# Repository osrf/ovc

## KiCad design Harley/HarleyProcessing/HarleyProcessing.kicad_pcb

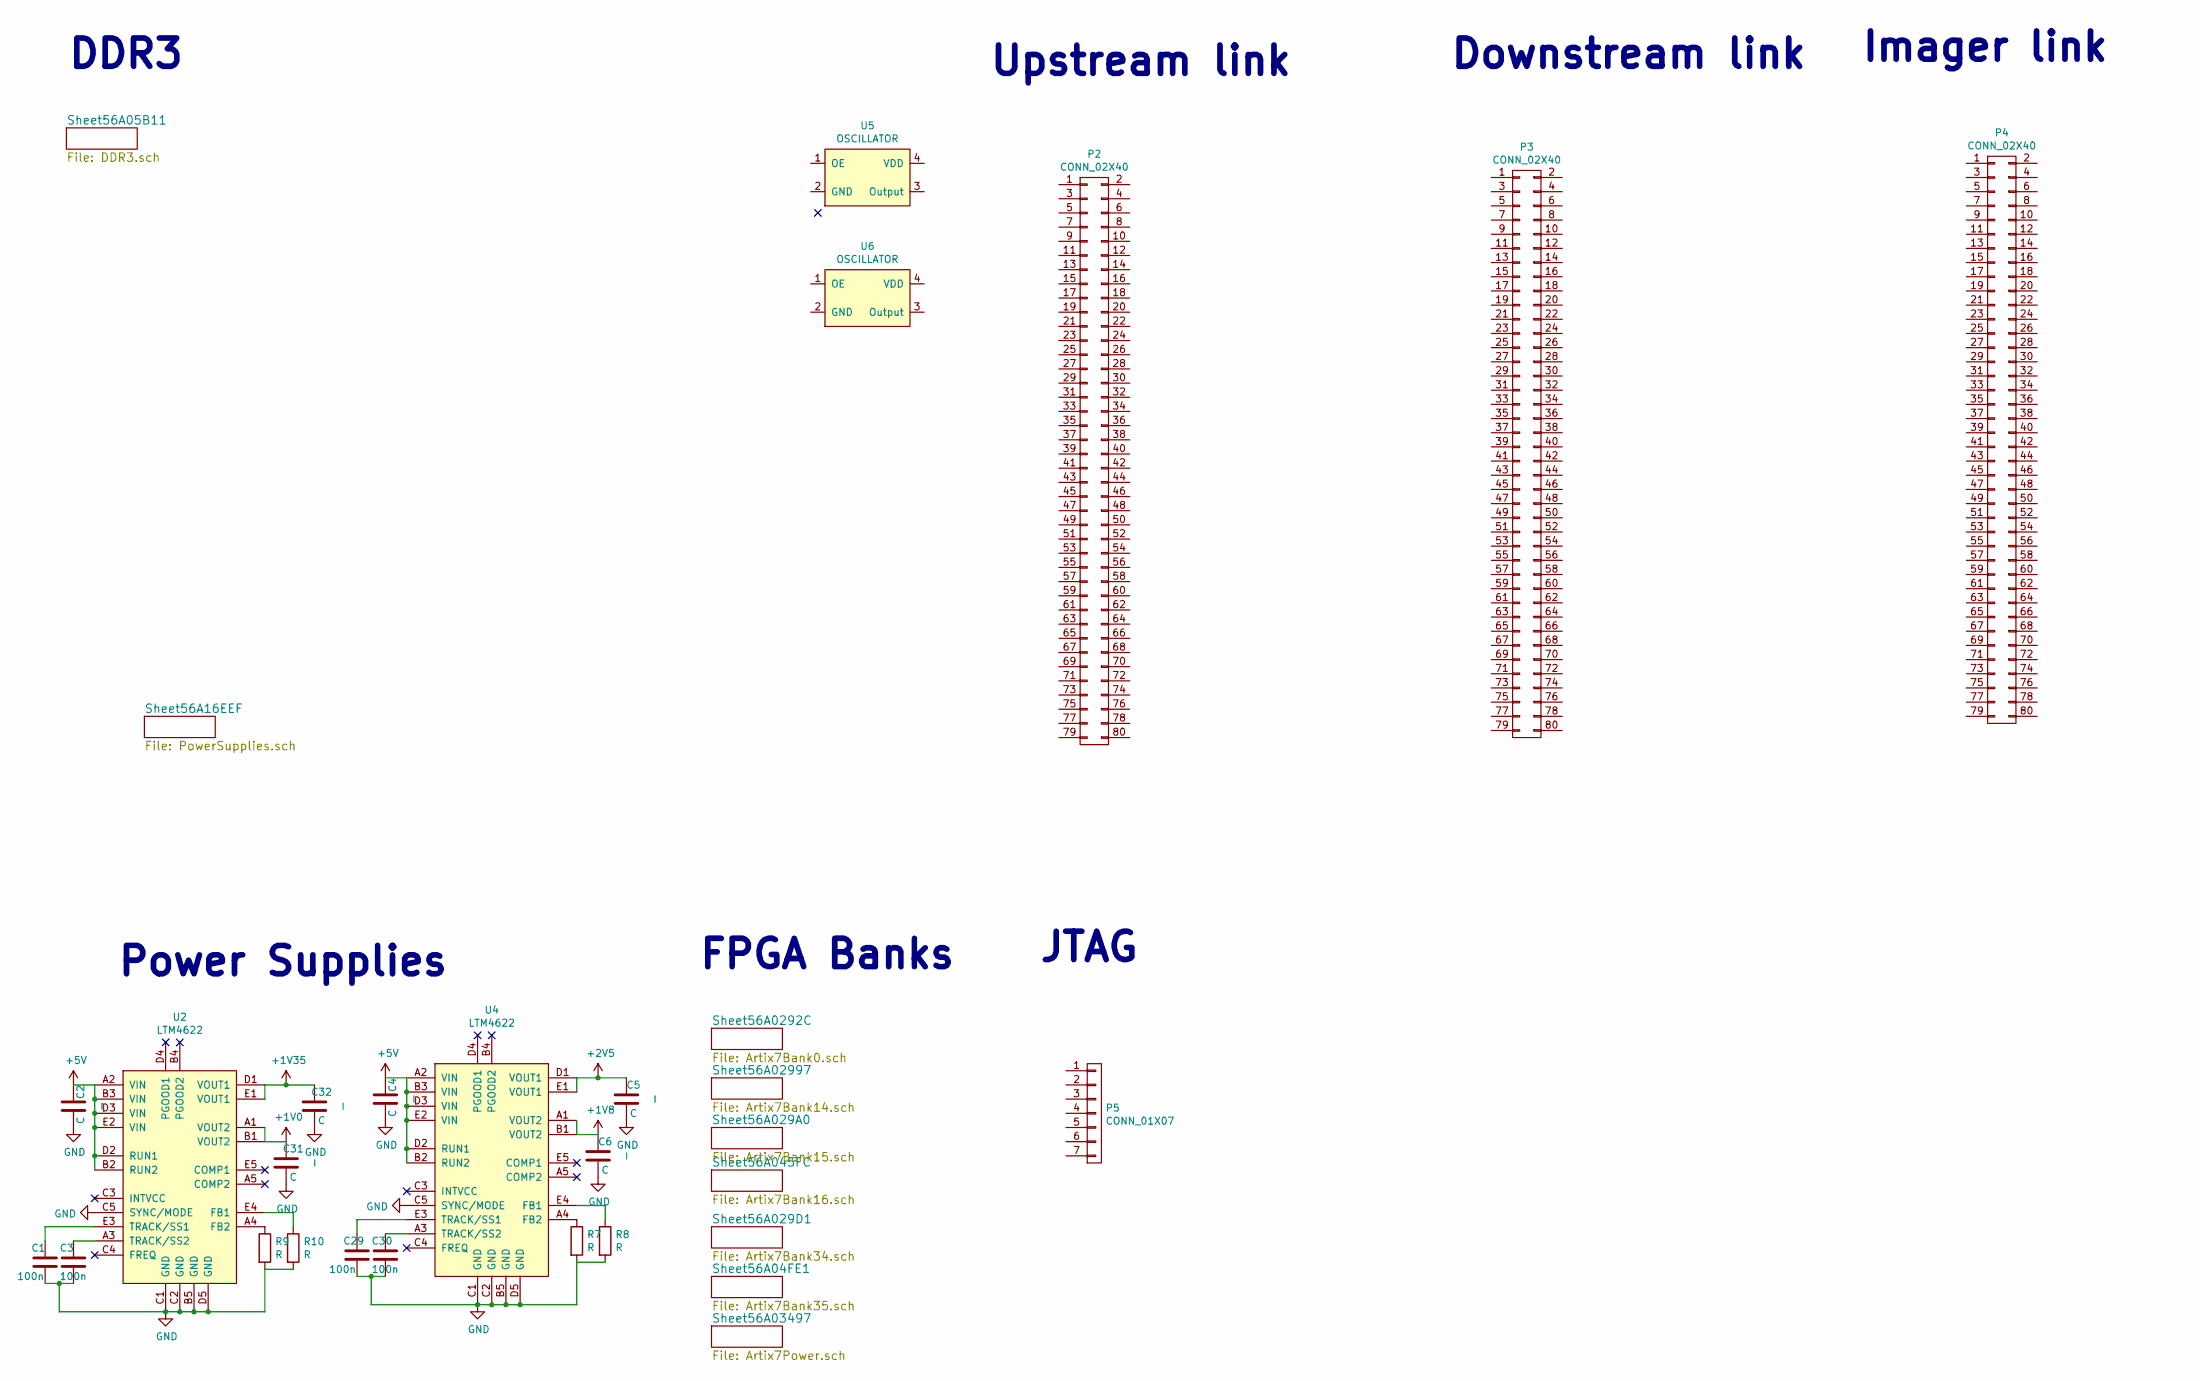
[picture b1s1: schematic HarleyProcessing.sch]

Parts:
C1, C3, C29, C30: 100n; C_0402
C2, C4: C; C_0603; Voltage _; Tolerance _
C5, C6, C31, C32: C; C_0805; Voltage _; Tolerance _
P2, P3, P4: CONN_02X40; DF40C_80DS_0-4V
P5: CONN_01X07; Pin_Header_Straight_1x07
R7, R8, R9, R10: R; R_0402
U2, U4: LTM4622; LGA25_6.25X6.25X1.82; Voltage _; Tolerance _
U5, U6: OSCILLATOR; 8y; Voltage _; Tolerance _

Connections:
+1V0: C31.2, U2.A1 (VOUT2), U2.B1 (VOUT2)
+1V8: C6.2, U4.A1 (VOUT2), U4.B1 (VOUT2)
+1V35: C32.2, U2.D1 (VOUT1), U2.E1 (VOUT1)
+2V5: C5.2, U4.D1 (VOUT1), U4.E1 (VOUT1)
+5V: C2.2, C4.2, U2.A2 (VIN), U2.B2 (RUN2), U2.B3 (VIN), U2.D2 (RUN1), U2.D3 (VIN), U2.E2 (VIN), U4.A2 (VIN), U4.B2 (RUN2), U4.B3 (VIN), U4.D2 (RUN1), U4.D3 (VIN), U4.E2 (VIN)
GND: C1.2, C2.1, C3.2, C4.1, C5.1, C6.1, C29.2, C30.2, C31.1, C32.1, R7.2, R8.2, R9.2, R10.2, U2.B5 (GND), U2.C1 (GND), U2.C2 (GND), U2.C5 (SYNC/MODE), U2.D5 (GND), U4.B5 (GND), U4.C1 (GND), U4.C2 (GND), U4.C5 (SYNC/MODE), U4.D5 (GND); also elsewhere on the board
unnamed: C1.1, U2.E3 (TRACK/SS1)
unnamed: C3.1, U2.A3 (TRACK/SS2)
unnamed: C29.1, U4.E3 (TRACK/SS1)
unnamed: C30.1, U4.A3 (TRACK/SS2)
unnamed: R7.1, U4.A4 (FB2)
unnamed: R8.1, U4.E4 (FB1)
unnamed: R9.1, U2.A4 (FB2)
unnamed: R10.1, U2.E4 (FB1)

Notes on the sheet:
Power Supplies
FPGA Banks
Upstream link
Downstream link
JTAG
Imager link
DDR3

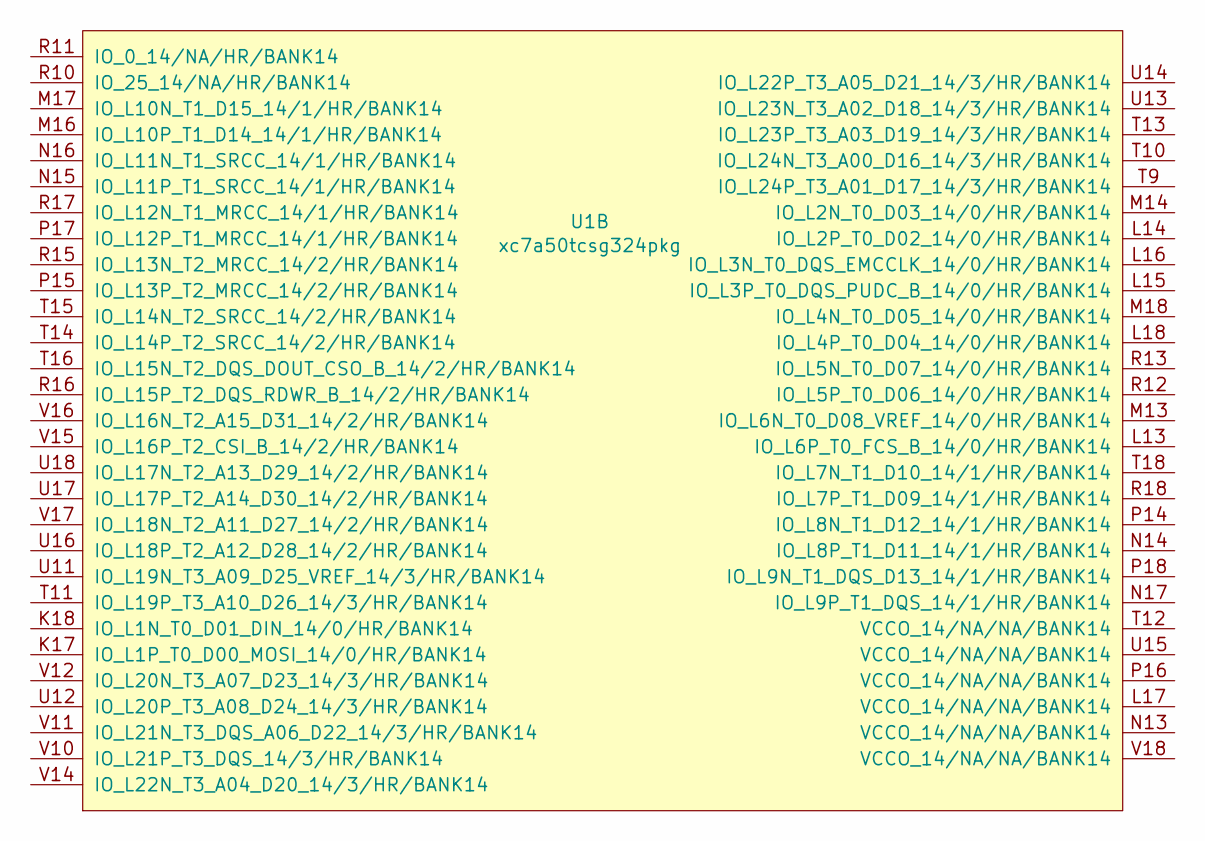
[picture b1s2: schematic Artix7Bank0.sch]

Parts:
U1: xc7a50tcsg324pkg; BGA324C80P18X18_1500X1500X150; Voltage _; Tolerance _

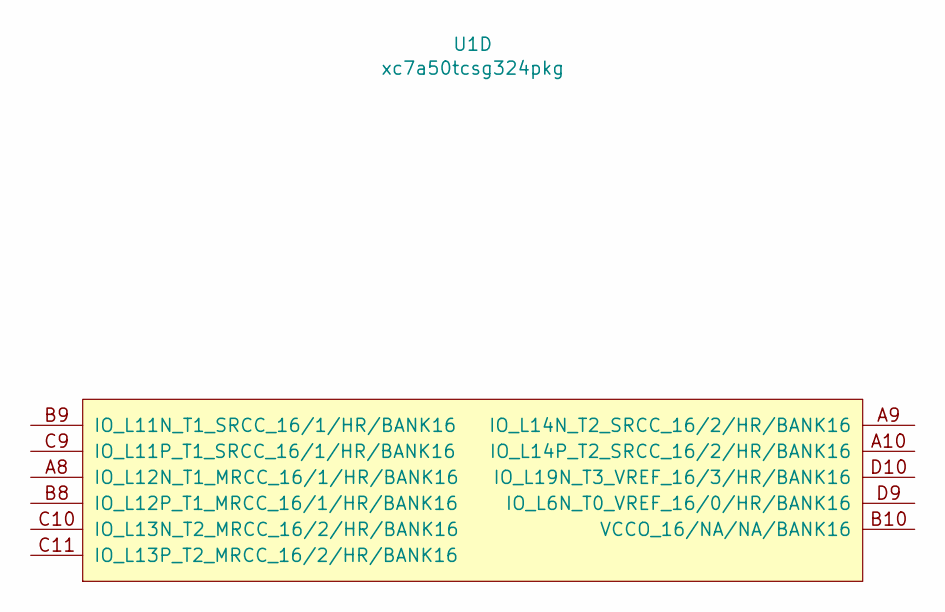
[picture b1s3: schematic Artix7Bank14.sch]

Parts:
U1: xc7a50tcsg324pkg; BGA324C80P18X18_1500X1500X150; Voltage _; Tolerance _

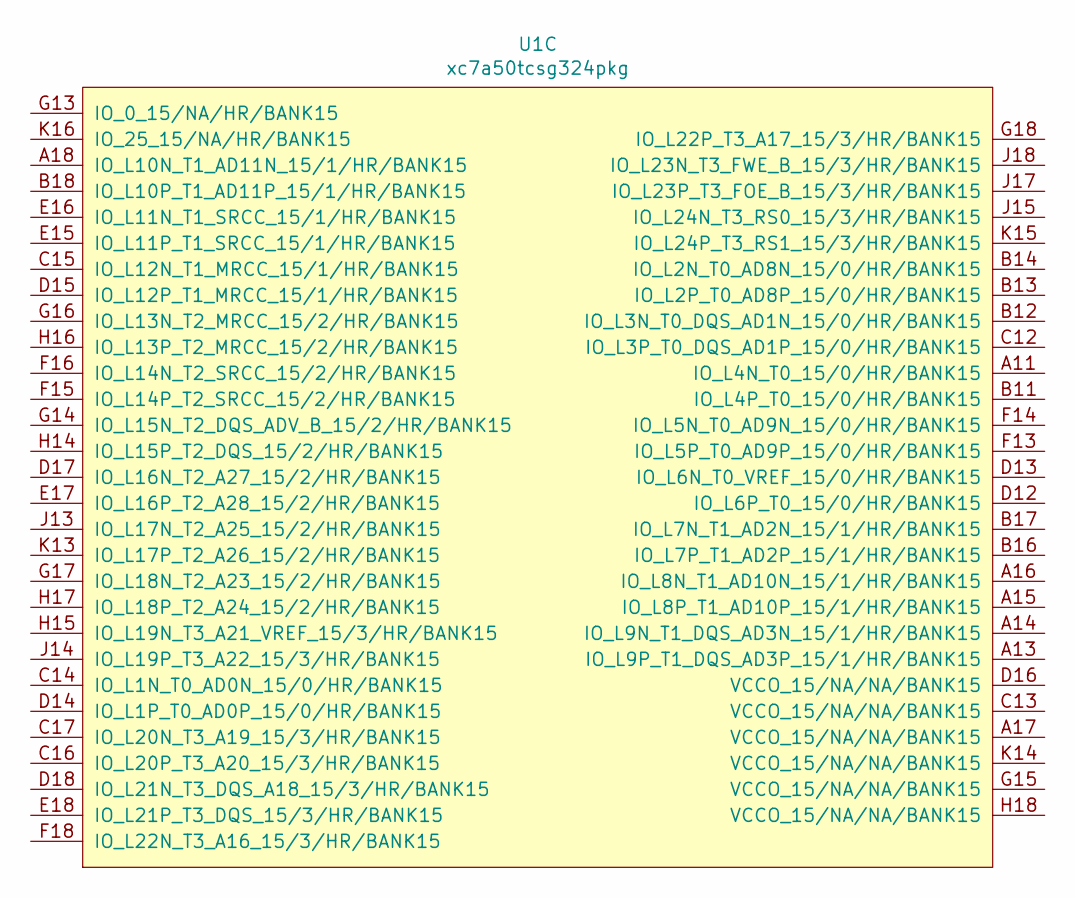
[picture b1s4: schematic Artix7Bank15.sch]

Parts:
U1: xc7a50tcsg324pkg; BGA324C80P18X18_1500X1500X150; Voltage _; Tolerance _

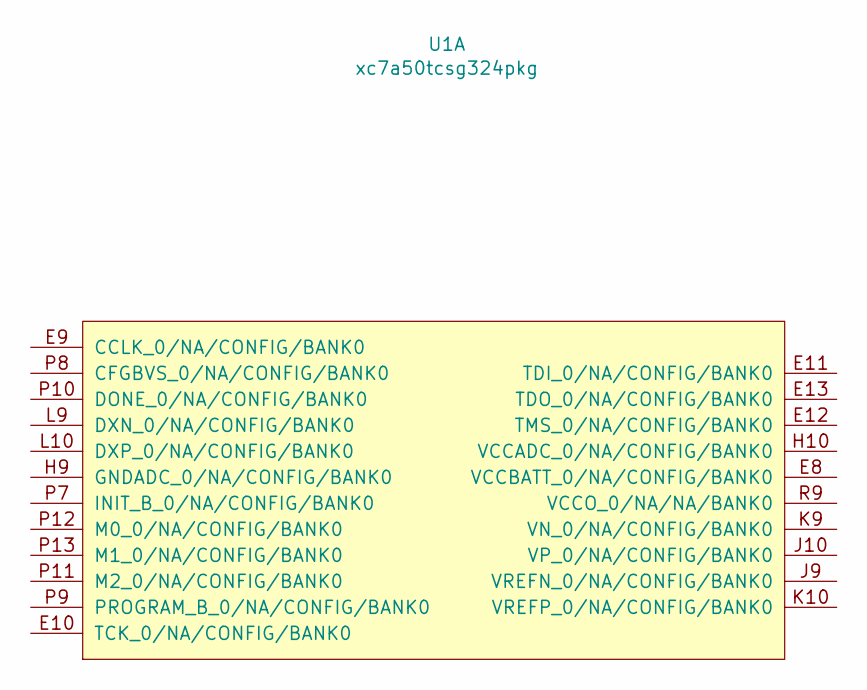
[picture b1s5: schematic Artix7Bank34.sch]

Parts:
U1: xc7a50tcsg324pkg; BGA324C80P18X18_1500X1500X150; Voltage _; Tolerance _

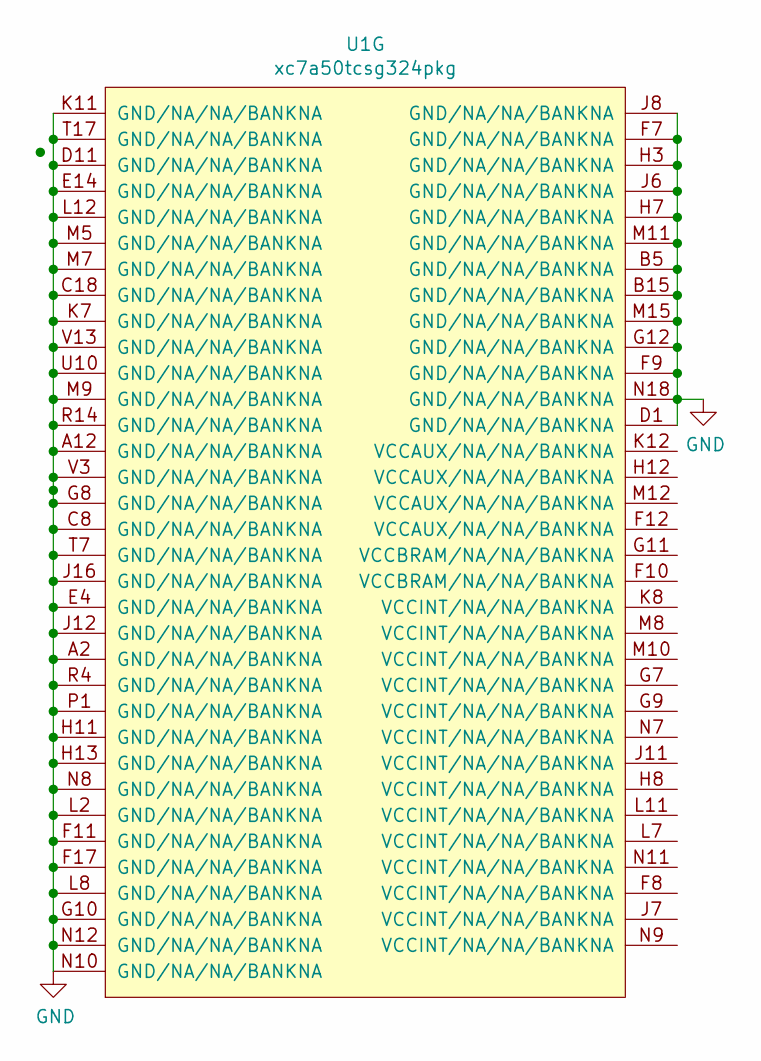
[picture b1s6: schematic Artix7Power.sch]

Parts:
U1: xc7a50tcsg324pkg; BGA324C80P18X18_1500X1500X150; Voltage _; Tolerance _

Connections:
GND: U1.A2 (GND/NA/NA/BANKNA), U1.A12 (GND/NA/NA/BANKNA), U1.B5 (GND/NA/NA/BANKNA), U1.B15 (GND/NA/NA/BANKNA), U1.C8 (GND/NA/NA/BANKNA), U1.C18 (GND/NA/NA/BANKNA), U1.D1 (GND/NA/NA/BANKNA), U1.D11 (GND/NA/NA/BANKNA), U1.E4 (GND/NA/NA/BANKNA), U1.E14 (GND/NA/NA/BANKNA), U1.F7 (GND/NA/NA/BANKNA), U1.F9 (GND/NA/NA/BANKNA), U1.F11 (GND/NA/NA/BANKNA), U1.F17 (GND/NA/NA/BANKNA), U1.G8 (GND/NA/NA/BANKNA), U1.G10 (GND/NA/NA/BANKNA), U1.G12 (GND/NA/NA/BANKNA), U1.H3 (GND/NA/NA/BANKNA), U1.H7 (GND/NA/NA/BANKNA), U1.H11 (GND/NA/NA/BANKNA), U1.H13 (GND/NA/NA/BANKNA), U1.J6 (GND/NA/NA/BANKNA), U1.J8 (GND/NA/NA/BANKNA), U1.J12 (GND/NA/NA/BANKNA), U1.J16 (GND/NA/NA/BANKNA), U1.K7 (GND/NA/NA/BANKNA), U1.K11 (GND/NA/NA/BANKNA), U1.L2 (GND/NA/NA/BANKNA), U1.L8 (GND/NA/NA/BANKNA), U1.L12 (GND/NA/NA/BANKNA), U1.M5 (GND/NA/NA/BANKNA), U1.M7 (GND/NA/NA/BANKNA), U1.M9 (GND/NA/NA/BANKNA), U1.M11 (GND/NA/NA/BANKNA), U1.M15 (GND/NA/NA/BANKNA), U1.N8 (GND/NA/NA/BANKNA), U1.N10 (GND/NA/NA/BANKNA), U1.N12 (GND/NA/NA/BANKNA), U1.N18 (GND/NA/NA/BANKNA), U1.P1 (GND/NA/NA/BANKNA), U1.R4 (GND/NA/NA/BANKNA), U1.R14 (GND/NA/NA/BANKNA), U1.T7 (GND/NA/NA/BANKNA), U1.T17 (GND/NA/NA/BANKNA), U1.U10 (GND/NA/NA/BANKNA), U1.V3 (GND/NA/NA/BANKNA), U1.V13 (GND/NA/NA/BANKNA); also elsewhere on the board

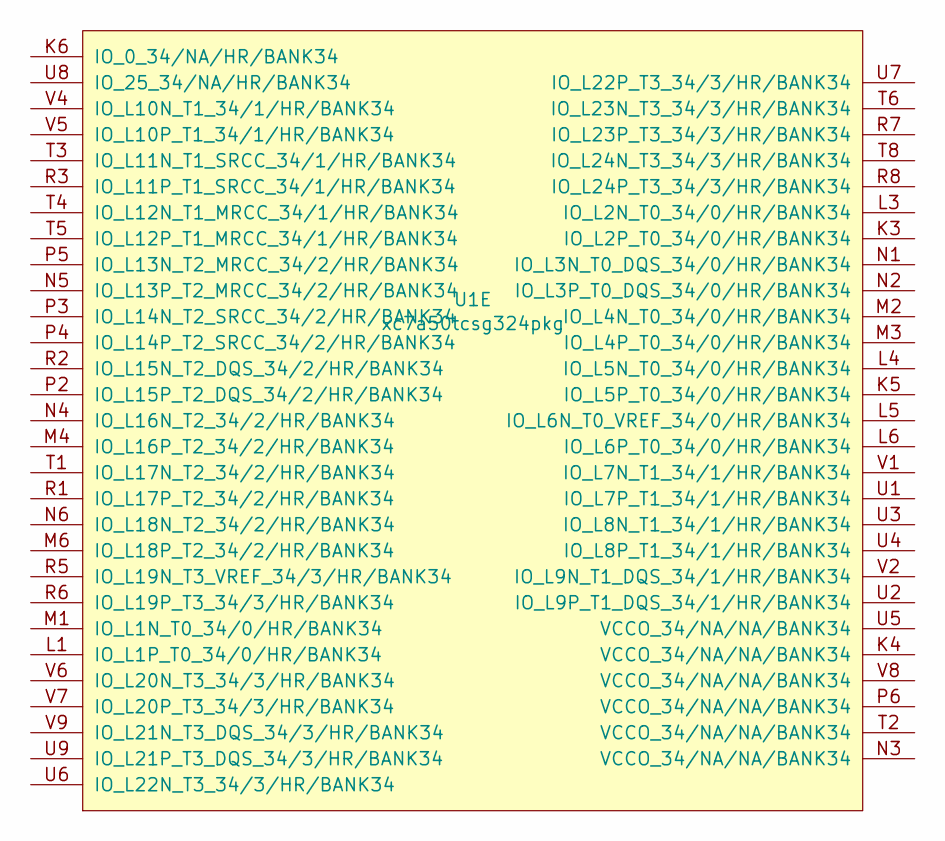
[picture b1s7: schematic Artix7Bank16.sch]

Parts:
U1: xc7a50tcsg324pkg; BGA324C80P18X18_1500X1500X150; Voltage _; Tolerance _

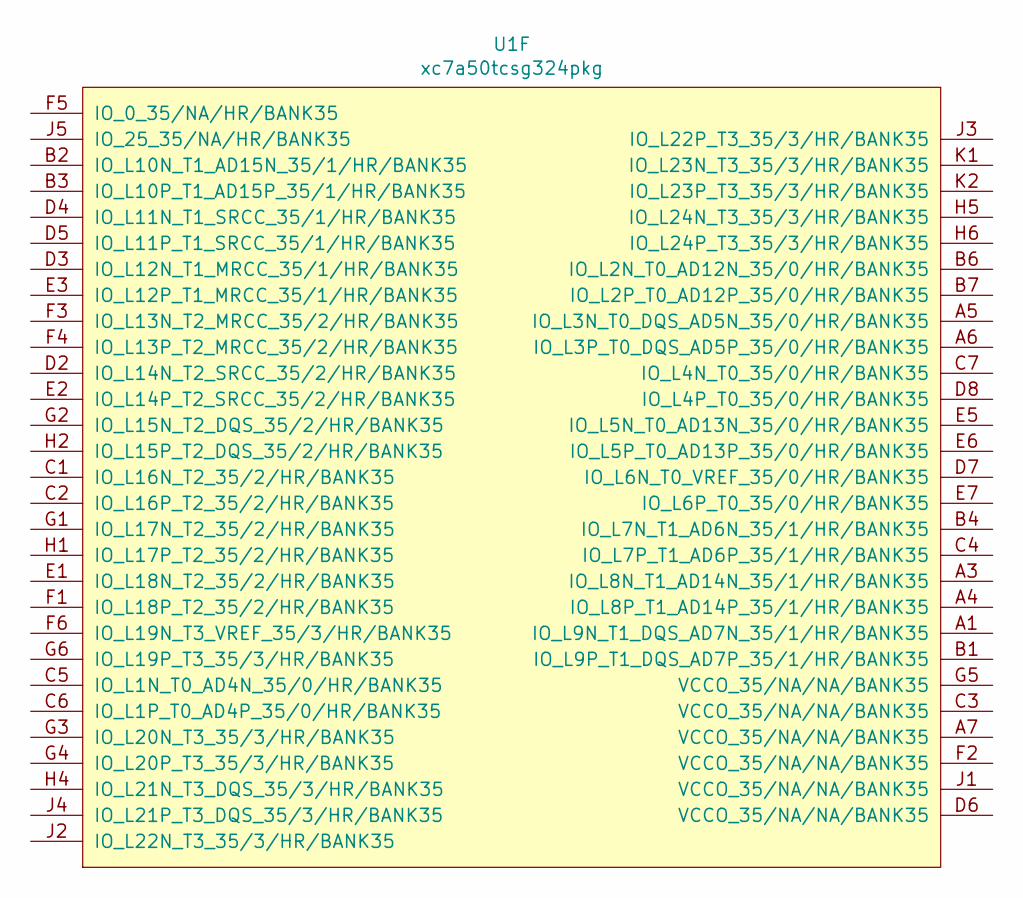
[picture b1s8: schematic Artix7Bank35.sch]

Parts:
U1: xc7a50tcsg324pkg; BGA324C80P18X18_1500X1500X150; Voltage _; Tolerance _

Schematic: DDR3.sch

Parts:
C7, C23: 1u; C_0201; Voltage 6.3; Tolerance 20%
C8, C10, C12, C27, C28: 10n; C_0201; Voltage 10; Tolerance 10%
C9, C11, C13, C15, C17, C19: 2.2n; C_0201; Voltage 25; Tolerance 10%
C14, C16, C18: 100n; C_0201; Voltage 6.3; Tolerance 10%
C20, C22, C25: 470n; C_0201; Voltage 6.3; Tolerance 10%
C21: 3.3n; C_0201; Voltage 25; Tolerance 10%
C24: 4.7n; C_0201; Voltage 16; Tolerance 10%
C26: 22u; C_0805; Voltage 6.3; Tolerance 10%
R1: 4.7k; C_0201; Voltage _; Tolerance 1%
R2: 80.6; R_0402; Voltage _; Tolerance 1%
R3, R4: 1k; C_0201; Voltage _; Tolerance 1%
R5: 240; C_0201; Voltage _; Tolerance 1%
R6: 2k; C_0201; Voltage _; Tolerance 1%
U3: MT41K128M16; WBGA96C80P6X16_90X1300X120; Voltage _; Tolerance _

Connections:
DDR_A0: U3.N3 (A0)
DDR_A1: U3.P7 (A1)
DDR_A2: U3.P3 (A2)
DDR_A3: U3.N2 (A3)
DDR_A4: U3.P8 (A4)
DDR_A5: U3.P2 (A5)
DDR_A6: U3.R8 (A6)
DDR_A7: U3.R2 (A7)
DDR_A8: U3.T8 (A8)
DDR_A9: U3.R3 (A9)
DDR_A10: U3.L7 (A10/AP)
DDR_A11: U3.R7 (A11)
DDR_A12: U3.N7 (A12/BC#)
DDR_A13: U3.T3 (A13)
DDR_BA0: U3.M2 (BA0)
DDR_BA1: U3.N8 (BA1)
DDR_BA2: U3.M3 (BA2)
DDR_CAS#: U3.K3 (CAS#)
DDR_CKE: R1.1, U3.K9 (CKE)
DDR_CLK+: R2.1, U3.J7 (CK+)
DDR_CLK-: R2.2, U3.K7 (CK-)
DDR_DQL0: U3.E3 (DQL0)
DDR_DQL1: U3.F7 (DQL1)
DDR_DQL2: U3.F2 (DQL2)
DDR_DQL3: U3.F8 (DQL3)
DDR_DQL4: U3.H3 (DQL4)
DDR_DQL5: U3.H8 (DQL5)
DDR_DQL6: U3.G2 (DQL6)
DDR_DQL7: U3.H7 (DQL7)
DDR_DQSL+: U3.F3 (DQSL+)
DDR_DQSL-: U3.G3 (DQSL-)
DDR_DQSU+: U3.C7 (DQSU+)
DDR_DQSU-: U3.B7 (DQSU-)
DDR_DQU0: U3.D7 (DQU0)
DDR_DQU1: U3.C3 (DQU1)
DDR_DQU2: U3.C8 (DQU2)
DDR_DQU3: U3.C2 (DQU3)
DDR_DQU4: U3.A7 (DQU4)
DDR_DQU5: U3.A2 (DQU5)
DDR_DQU6: U3.B8 (DQU6)
DDR_DQU7: U3.A3 (DQU7)
DDR_ODT: U3.K1 (ODT)
DDR_RAS#: U3.J3 (RAS#)
DDR_RST#: R6.2, U3.T2 (RST#)
DDR_VDD: C9.1, C10.1, C11.1, C12.1, C13.1, C14.1, C15.1, C16.1, C17.1, C18.1, C19.1, C20.1, C21.1, C22.1, C23.1, C24.1, C25.1, C26.1, C27.1, C28.1, R3.1, R6.1, U3.A1 (VDDQ), U3.A8 (VDDQ), U3.B2 (VDD), U3.C1 (VDDQ), U3.C9 (VDDQ), U3.D2 (VDDQ), U3.D9 (VDD), U3.E9 (VDDQ), U3.F1 (VDDQ), U3.G7 (VDD), U3.H2 (VDDQ), U3.H9 (VDDQ), U3.K2 (VDD), U3.K8 (VDD), U3.N1 (VDD), U3.N9 (VDD), U3.R1 (VDD), U3.R9 (VDD)
DDR_VREF: C7.1, C8.1, R3.2, R4.1, U3.H1 (VREFDQ), U3.M8 (VREFCA)
DDR_WE#: U3.L3 (WE#)
GND: C7.2, C8.2, C9.2, C10.2, C11.2, C12.2, C13.2, C14.2, C15.2, C16.2, C17.2, C18.2, C19.2, C20.2, C21.2, C22.2, C23.2, C24.2, C25.2, C26.2, C27.2, C28.2, R1.2, R4.2, R5.2, U3.A9 (VSS), U3.B1 (VSSQ), U3.B3 (VSS), U3.B9 (VSSQ), U3.D1 (VSSQ), U3.D3 (DMU), U3.D8 (VSSQ), U3.E1 (VSS), U3.E2 (VSSQ), U3.E7 (DML), U3.E8 (VSSQ), U3.F9 (VSSQ), U3.G1 (VSSQ), U3.G8 (VSS), U3.G9 (VSSQ), U3.J2 (VSS), U3.J8 (VSS), U3.L2 (CS#), U3.M1 (VSS), U3.M9 (VSS), U3.P1 (VSS), U3.P9 (VSS), U3.T1 (VSS), U3.T9 (VSS); also elsewhere on the board
unnamed: R5.1, U3.L8 (ZQ)

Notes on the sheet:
SDRAM DDR3L

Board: 2 copper layers, 51 parts (1 on the bottom side), 21 nets, no tracks yet.

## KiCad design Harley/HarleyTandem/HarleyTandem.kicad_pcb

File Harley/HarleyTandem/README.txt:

Project: harley_tandem, rev. B
(This is a trinocular camera sensor board.)

=============================
PCB Fabrication notes:
=============================
* Lead time: 4 days
* Board outline is a rectangle with a rectangular protrusion on the north side.
* Bounding box is 9.40" x 1.54"
* 6 layers:
  * layer 1 = signal with 7-mil 50-ohm traces relative to layer 2
  * layer 2 = full plane
  * layer 3 = mixed (signal and partial planes)
  * layer 4 = mixed (signal and partial planes)
  * layer 5 = full plane
  * layer 6 = signal with 7-mil 50-ohm traces relative to layer 5
* Controlled stackup, using the included "harley_tandem_stackup_rev_b.pdf" report
  generated by Sierra's "HDI Stackup Planner" website. PLEASE NOTE however that
  I was unable to generate the report I wanted from the website; we want 7-mil
  traces on the outer layers (1 & 6) to be 50 ohm +/- 10% with respect to the
  planes on layers 2 & 5. This will likely need a slightly different stackup
  than that shown on the report.
  * 61mil PCB thickness.
  * 7mil traces on outer layer (1 & 6) need to be 50 ohm +/- 10% with respect to
    the planes on layers 2 & 5. The dielectric thickness between
    layers 1&2 and 5&6 will likely need to be slightly thicker than shown on
    the report to get within 10% (or better) of 50mil impedance.
* Layer thicknesses as specified in the stackup report: { 1, 1, 0.5, 0.5, 1, 1 }
* Minimum trace/space is 5mil.
* All holes plated
* Minimum via-drill 8 mil, minimum via-pad 16 mil. Most vias are >= 24mil
* FR4 material
* HASL finish
* Green soldermask both sides
* White silkscreen both sides
* RoHS processing is fine but not necessary; these are laboratory prototypes.

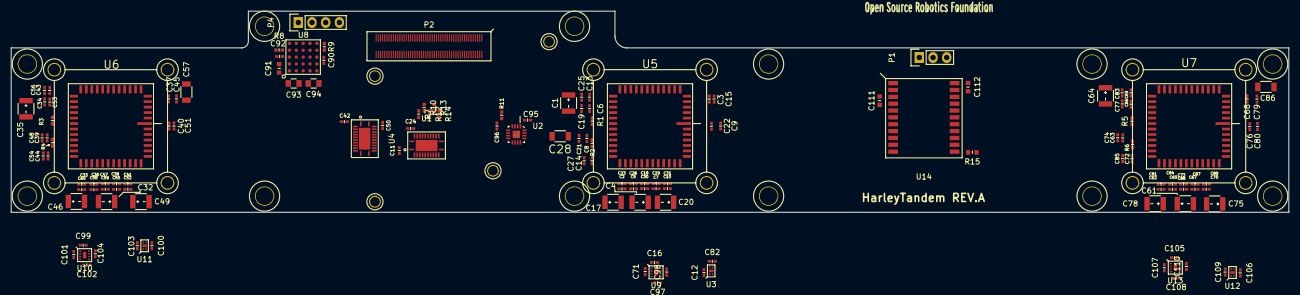
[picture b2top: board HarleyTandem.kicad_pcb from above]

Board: 6 copper layers, 237.0 x 37.3 mm, 144 parts (0 on the bottom side), 100 nets, no tracks yet.

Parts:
C1, C4, C17, C20, C32, C35, C46, C49, C61, C64, C75, C78: 100u; C_1210Polarized
C2, C5, C7, C10, C15, C19, C21, C22, C25, C27, C30, C33, C36, C38, C41, C45, C48, C51, C53, C54, C56, C59, C62, C65, C67, C70, C74, C77, C79, C80, C83, C85, C88: 4.7u; C_0402
C3, C6, C8, C11, C24, C34, C37, C39, C42, C50, C63, C66, C68, C71, C101, C107: 100n; C_0402
C9, C12, C13, C14, C16, C18, C23, C26, C29, C31, C40, C43, C44, C47, C52, C55, C58, C60, C69, C72, C73, C76, C81, C82, C84, C87, C89, C95, C96, C97, C98, C99, C100, C102, C103, C104, C105, C106, C108, C109, C110: 1u; C_0402
C28, C57, C86: 10u; C_1206
C90, C92: 10n; C_0402
C91: 10u; C_0603
C93, C94: 47u; C_0805
C111, C112: 100n; C_0603
P1: CONN_01X03; Pin_Header_Straight_1x03
P2: CONN_02X50; DF40C_100DS_0-4V
P4: CONN_01X04; Pin_Header_Straight_1x04
R1, R3, R5, R11: 100; R_0402
R2, R4, R6: 47k; R_0402
R7, R10, R12, R13, R14: 50; R_0402
R8: 12.4k; R_0402
R9: 25.5k; R_0402
R15: 10k; R_0603
U1, U4: 74AVCH8T245-1EP; QFN-24-1EP-Pitch0.5-nonSquare
U2: SI53306; QFN-16-1EP_3x3mm_Pitch0.5mm
U3, U11, U12: mic5302; MLF4
U5, U6, U7: NOIP1SN1300A-QDI; LCC101.6P1422X1422X165-48
U8: LTM4622; LGA25_6.25X6.25X1.82
U9, U10, U13: mic5330; MLF8
U14: uIMU-2; DFP-22_0.5mmPitch_125x155mm

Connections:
2V0: C12.1, C94.2, C100.1, C106.1, P4.3, U3.1, U3.3, U8.D1, U8.E1, U11.1, U11.3, U12.1, U12.3
3V5: C11.1, C16.1, C42.1, C93.2, C99.1, C105.1, C111.1, C112.1, P4.2, R15.1, U1.1, U4.1, U4.2, U8.A1, U8.B1, U9.1, U9.4, U9.5, U10.1, U10.4, U10.5, U13.1, U13.4, U13.5, U14.3, U14.22
+2V5: C24.1, C50.1, C95.2, C96.1, P2.81, P2.83, P2.85, U1.23, U1.24, U2.1, U2.5, U2.16, U4.23, U4.24
+5V: C91.2, P2.87, P2.89, P2.91, P2.93, P2.95, P2.97, P2.99, P4.1, U8.A2, U8.B2, U8.B3, U8.D2, U8.D3, U8.E2
GND: C1.2, C2.2, C3.2, C4.2, C5.2, C6.2, C7.2, C8.2, C9.2, C10.2, C11.2, C12.2, C13.2, C14.2, C15.2, C16.2, C17.2, C18.2, C19.2, C20.2, C21.2, C22.2, C23.2, C24.2, C25.2, C26.2, C27.2, C28.2, C29.2, C30.2, C31.2, C32.2, C33.2, C34.2, C35.2, C36.2, C37.2, C38.2, C39.2, C40.2, C41.2, C42.2, C43.2, C44.2, C45.2, C46.2, C47.2, C48.2, C49.2, C50.2, C51.2, C52.2, C53.2, C54.2, C55.2, C56.2, C57.2, C58.2, C59.2, C60.2, C61.2, C62.2, C63.2, C64.2, C65.2, C66.2, C67.2, C68.2, C69.2, C70.2, C71.2, C72.2, C73.2, C74.2, C75.2, C76.2, C77.2, C78.2, C79.2, C80.2, C81.2, C82.2, C83.2, C84.2, C85.2, C86.2, C87.2, C88.2, C89.2, C90.2, C91.1, C92.2, C93.1, C94.1, C95.1, C96.2, C97.2, C98.2, C99.2, C100.2, C101.2, C102.2, C103.2, C104.2, C105.2, C106.2, C107.2, C108.2, C109.2, C110.2, C111.2, C112.2, P1.3, P2.1, P2.3, P2.5, P2.6, P2.7, P2.12, P2.13, P2.18, P2.19, P2.24, P2.25, P2.30, P2.31, P2.36, P2.37, P2.42, P2.43, P2.48, P2.49, P2.54, P2.60, P2.66, P2.72, P2.79, P2.86, P2.90, P4.4, R2.2, R4.2, R6.2, R8.2, R9.2, U1.2, U1.11, U1.12, U1.13, U1.22, U1.25, U2.4, U2.8, U2.13, U2.17, U3.2, U3.EPAD, U4.11, U4.12, U4.13, U4.14, U4.15, U4.21, U4.22, U4.25, U5.5, U5.20, U5.21, U5.25, U5.27, U5.30, U5.32, U5.34, U5.35, U5.37, U5.39, U5.42, U5.43, U5.48, U6.5, U6.20, U6.21, U6.25, U6.27, U6.30, U6.32, U6.34, U6.35, U6.37, U6.39, U6.42, U6.43, U6.48, U7.5, U7.20, U7.21, U7.25, U7.27, U7.30, U7.32, U7.34, U7.35, U7.37, U7.39, U7.42, U7.43, U7.48, U8.B5, U8.C1, U8.C2, U8.D5, U9.2, U9.EPAD, U10.2, U10.EPAD, U11.2, U11.EPAD, U12.2, U12.EPAD, U13.2, U13.EPAD, U14.11, U14.21
IMU_RX0: P1.2, U14.18
IMU_RX1: U1.10, U14.6
IMU_TX0: P1.1, U14.19
IMU_TX1: U4.8, U14.7
unnamed: C71.1, U9.3
unnamed: C90.1, U8.E3
unnamed: C92.1, U8.A3
unnamed: C101.1, U10.3
unnamed: C107.1, U13.3
unnamed: R2.1, U5.28
unnamed: R4.1, U6.28
unnamed: R6.1, U7.28
unnamed: R7.2, U1.21
unnamed: R8.1, U8.A4
unnamed: R9.1, U8.E4
unnamed: R10.2, U1.20
unnamed: R12.2, U1.19
unnamed: R13.2, U1.18
unnamed: R14.2, U1.17
unnamed: R15.2, U14.12
Python1_1V8: C3.1, C6.1, C8.1, C15.1, C19.1, C21.1, C28.1, C82.1, U3.4, U5.6, U5.22, U5.26
Python1_CS#: P2.82, R13.1
Python1_CS#_3V3: U1.6, U5.47
Python1_DOUT0+: P2.44, U5.9
Python1_DOUT0-: P2.46, U5.10
Python1_DOUT1+: P2.50, U5.11
Python1_DOUT1-: P2.52, U5.12
Python1_DOUT2+: P2.56, U5.13
Python1_DOUT2-: P2.58, U5.14
Python1_DOUT3+: P2.62, U5.15
Python1_DOUT3-: P2.64, U5.16
Python1_Monitor: P2.96, U4.18
Python1_Monitor_3V3: U4.6, U5.44
Python1_SYNC+: P2.68, U5.17
Python1_SYNC-: P2.70, U5.18
Python1_VDD: C1.1, C4.1, C9.1, C13.1, C14.1, C18.1, C22.1, C25.1, C27.1, C30.1, C97.1, U5.1, U5.19, U5.29, U5.36, U9.8
Python1_VDDPIX: C2.1, C5.1, C7.1, C10.1, C17.1, C20.1, C23.1, C26.1, C29.1, C31.1, C98.1, U5.31, U5.33, U5.38, U5.40, U9.7
Python1_clk_return+: P2.38, U5.7
Python1_clk_return-: P2.40, U5.8
Python1_lvds_clk+: R1.2, U2.14, U5.24
Python1_lvds_clk-: R1.1, U2.15, U5.23
Python2_1V8: C34.1, C37.1, C39.1, C45.1, C48.1, C53.1, C57.1, C103.1, U6.6, U6.22, U6.26, U11.4
Python2_CS#: P2.84, R12.1
Python2_CS#_3V3: U1.5, U6.47
Python2_DOUT0+: P2.17, U6.9
Python2_DOUT0-: P2.15, U6.10
Python2_DOUT1+: P2.11, U6.11
Python2_DOUT1-: P2.9, U6.12
Python2_DOUT2+: P2.21, U6.13
Python2_DOUT2-: P2.23, U6.14
Python2_DOUT3+: P2.27, U6.15
Python2_DOUT3-: P2.29, U6.16
Python2_Monitor: P2.98, U4.19
Python2_Monitor_3V3: U4.5, U6.44
Python2_SYNC+: P2.35, U6.17
Python2_SYNC-: P2.33, U6.18
Python2_VDD: C32.1, C35.1, C40.1, C43.1, C44.1, C47.1, C51.1, C54.1, C56.1, C59.1, C102.1, U6.1, U6.19, U6.29, U6.36, U10.8
Python2_VDDPIX: C33.1, C36.1, C38.1, C41.1, C46.1, C49.1, C52.1, C55.1, C58.1, C60.1, C104.1, U6.31, U6.33, U6.38, U6.40, U10.7
Python2_clk_return+: P2.39, U6.7
Python2_clk_return-: P2.41, U6.8
Python2_lvds_clk+: R3.2, U2.7, U6.24
Python2_lvds_clk-: R3.1, U2.6, U6.23
Python3_1V8: C63.1, C66.1, C68.1, C74.1, C77.1, C79.1, C86.1, C109.1, U7.6, U7.22, U7.26, U12.4
Python3_CS#: P2.80, R14.1
Python3_CS#_3V3: U1.7, U7.47
Python3_DOUT0+: P2.8, U7.9
Python3_DOUT0-: P2.10, U7.10
Python3_DOUT1+: P2.14, U7.11
Python3_DOUT1-: P2.16, U7.12
Python3_DOUT2+: P2.34, U7.13
Python3_DOUT2-: P2.32, U7.14
Python3_DOUT3+: P2.28, U7.15
Python3_DOUT3-: P2.26, U7.16
Python3_Monitor: P2.100, U4.20
Python3_Monitor_3V3: U4.4, U7.44
Python3_SYNC+: P2.22, U7.17
Python3_SYNC-: P2.20, U7.18
Python3_VDD: C61.1, C64.1, C69.1, C72.1, C73.1, C76.1, C80.1, C83.1, C85.1, C88.1, C108.1, U7.1, U7.19, U7.29, U7.36, U13.8
Python3_VDDPIX: C62.1, C65.1, C67.1, C70.1, C75.1, C78.1, C81.1, C84.1, C87.1, C89.1, C110.1, U7.31, U7.33, U7.38, U7.40, U13.7
Python3_clk_return+: P2.4, U7.7
Python3_clk_return-: P2.2, U7.8
Python3_lvds_clk+: R5.2, U2.11, U7.24
Python3_lvds_clk-: R5.1, U2.12, U7.23
Python_RST#: P2.74, U1.15
Python_RST#_3V3: U1.9, U5.46, U6.46, U7.46
Python_Trigger: P2.76, U1.16
Python_Trigger_3V3: U1.8, U5.41, U6.41, U7.41
Python_lvds_clk+: P2.45, R11.2, U2.3
Python_lvds_clk-: P2.47, R11.1, U2.2
SPI_MISO: P2.94, U4.17
SPI_MISO_3V3: U4.7, U5.3, U6.3, U7.3
SPI_MOSI: P2.92, R7.1
SPI_MOSI_3V3: U1.3, U5.2, U6.2, U7.2
SPI_SCK: P2.88, R10.1
SPI_SCK_3V3: U1.4, U5.4, U6.4, U7.4

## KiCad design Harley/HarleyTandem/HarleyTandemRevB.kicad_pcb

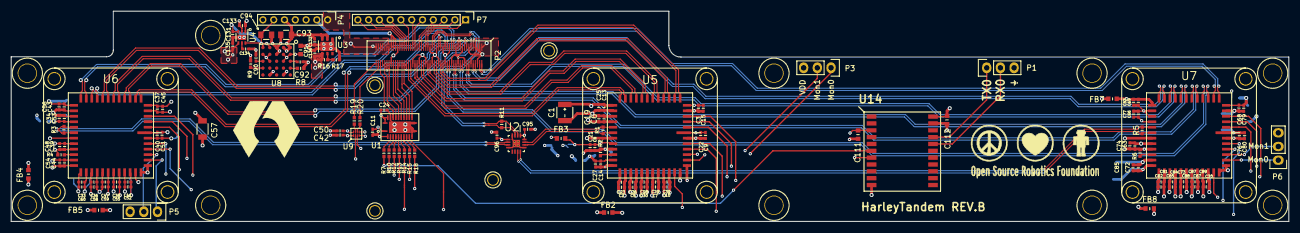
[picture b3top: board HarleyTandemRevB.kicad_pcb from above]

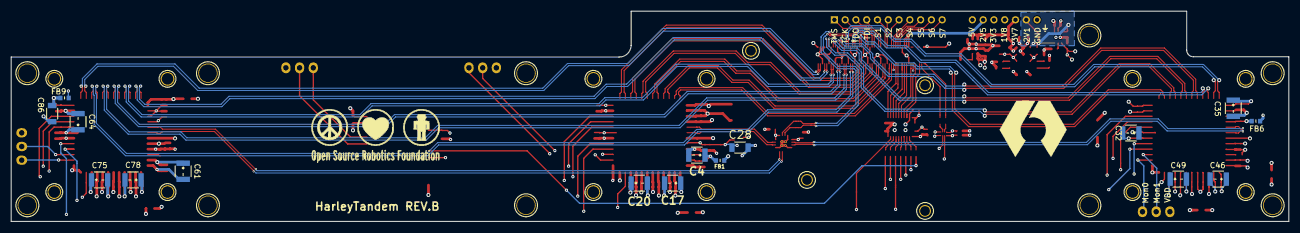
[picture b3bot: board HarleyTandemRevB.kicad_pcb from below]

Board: 6 copper layers, 237.0 x 39.0 mm, 146 parts (16 on the bottom side), 117 nets.

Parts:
C1, C4, C17, C20, C32, C35, C46, C49, C61, C64, C75, C78: 100u; C_1210Polarized
C2, C5, C7, C10, C15, C19, C21, C22, C25, C27, C30, C33, C36, C38, C41, C45, C48, C51, C53, C54, C56, C59, C62, C65, C67, C70, C74, C77, C79, C80, C83, C85, C88: 4.7u; C_0402
C3, C6, C8, C11, C24, C34, C37, C39, C42, C50, C63, C66, C68: 100n; C_0402
C9, C13, C14, C18, C23, C26, C29, C31, C40, C43, C44, C47, C52, C55, C58, C60, C69, C72, C73, C76, C81, C84, C87, C89, C95, C96, C131, C132, C133, C135: 1u; C_0402
C28, C57, C86: 10u; C_1206
C90, C92, C134: 10n; C_0402
C91: 10u; C_0603
C93, C94: 47u; C_0805
C111, C112: 100n; C_0603
C136: 2.2u; C_0402
FB1, FB3, FB4, FB6, FB7, FB9: 220; R_0603
FB2, FB5, FB8: 1k; R_0603
P1, P3, P5, P6: CONN_01X03; Pin_Header_Straight_1x03
P2: CONN_02X50; DF40C_100DS_0-4V
P4: CONN_01X07; Pin_Header_Straight_1x07_Pitch2.00mm
P7: CONN_01X11; Pin_Header_Straight_1x11_Pitch2.00mm
R1, R3, R5, R11: 100; R_0402
R2, R4, R6: 47k; R_0402
R7, R10, R12, R13, R14, R15, R18, R19, R20: 49.9; R_0402
R8: 11.5k; R_0402
R9: 24k; R_0402
R16: 8.06k; R_0402
R17: 4.7k; R_0402
U1: 74AVCH8T245-1EP; QFN-24-1EP-Pitch0.5-nonSquare
U2: SI53306; QFN-16-1EP_3x3mm_Pitch0.5mm
U3: LD39150PU; DFN-6-1EP_3x3mm_Pitch0.95mm
U4: mic5325; DFN-6-1EP_2x2mm_Pitch0.65mm
U5, U6, U7: NOIP1SN1300A-QDI; LCC101.6P1422X1422X165-48
U8: LTM4622; LGA25_6.25X6.25X1.82
U9: SN74AVC2T244; SON-N8-145x105
U14: uIMU-2; DFP-22_0.5mmPitch_125x155mm

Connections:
2V1: C94.2, C131.1, P4.6, U4.3, U4.6, U8.D1, U8.E1
3V7: C93.2, C132.1, P4.5, U3.2, U3.3, U8.A1, U8.B1
+1V8: C135.1, FB3.1, FB6.1, FB9.1, P4.4, U4.4
+2V5: C24.1, C50.1, C95.2, C96.1, P2.81, P2.83, P2.85, P4.2, U1.23, U1.24, U2.1, U2.5, U2.16, U9.8
+3V3: C11.1, C42.1, C111.1, C112.1, C133.1, C136.1, FB1.1, FB2.1, FB4.1, FB5.1, FB7.1, FB8.1, P4.3, R16.1, U1.1, U3.4, U4.1, U9.1, U14.3, U14.22
+5V: C91.2, P2.87, P2.89, P2.91, P2.93, P2.95, P2.97, P2.99, P4.1, U8.A2, U8.B2, U8.B3, U8.D2, U8.D3, U8.E2
FPGA_JTAG_TCK: P2.53, P7.2
FPGA_JTAG_TDI: P2.59, P7.4
FPGA_JTAG_TDO: P2.57, P7.3
FPGA_JTAG_TMS: P2.51, P7.1
FPGA_Signal1: P2.63, P7.5
FPGA_Signal2: P2.65, P7.6
FPGA_Signal3: P2.69, P7.7
FPGA_Signal4: P2.71, P7.8
FPGA_Signal5: P2.73, P7.9
FPGA_Signal6: P2.75, P7.10
FPGA_Signal7: P2.77, P7.11
GND: C1.2, C2.2, C3.2, C4.2, C5.2, C6.2, C7.2, C8.2, C9.2, C10.2, C11.2, C13.2, C14.2, C15.2, C17.2, C18.2, C19.2, C20.2, C21.2, C22.2, C23.2, C24.2, C25.2, C26.2, C27.2, C28.2, C29.2, C30.2, C31.2, C32.2, C33.2, C34.2, C35.2, C36.2, C37.2, C38.2, C39.2, C40.2, C41.2, C42.2, C43.2, C44.2, C45.2, C46.2, C47.2, C48.2, C49.2, C50.2, C51.2, C52.2, C53.2, C54.2, C55.2, C56.2, C57.2, C58.2, C59.2, C60.2, C61.2, C62.2, C63.2, C64.2, C65.2, C66.2, C67.2, C68.2, C69.2, C70.2, C72.2, C73.2, C74.2, C75.2, C76.2, C77.2, C78.2, C79.2, C80.2, C81.2, C83.2, C84.2, C85.2, C86.2, C87.2, C88.2, C89.2, C90.2, C91.1, C92.2, C93.1, C94.1, C95.1, C96.2, C111.2, C112.2, C131.2, C132.2, C133.2, C134.2, C135.2, C136.2, P1.3, P2.1, P2.3, P2.5, P2.6, P2.7, P2.12, P2.13, P2.18, P2.19, P2.24, P2.25, P2.30, P2.31, P2.36, P2.37, P2.42, P2.43, P2.48, P2.49, P2.54, P2.60, P2.66, P2.72, P2.79, P2.86, P2.90, P4.7, R2.2, R4.2, R6.2, R8.2, R9.2, R17.2, U1.2, U1.11, U1.12, U1.13, U1.22, U1.25, U2.4, U2.8, U2.13, U2.17, U3.1, U3.7, U4.2, U4.7, U5.5, U5.20, U5.21, U5.25, U5.27, U5.30, U5.32, U5.34, U5.35, U5.37, U5.39, U5.42, U5.43, U5.48, U6.5, U6.20, U6.21, U6.25, U6.27, U6.30, U6.32, U6.34, U6.35, U6.37, U6.39, U6.42, U6.43, U6.48, U7.5, U7.20, U7.21, U7.25, U7.27, U7.30, U7.32, U7.34, U7.35, U7.37, U7.39, U7.42, U7.43, U7.48, U8.B5, U8.C1, U8.C2, U8.D5, U9.4, U9.5, U14.11, U14.21
IMU_RX0: P1.2, U14.18
IMU_RX1: R7.2, U14.6
IMU_RX1_2V5: P2.96, U1.21
IMU_TX0: P1.1, U14.19
IMU_TX1: U9.3, U14.7
IMU_TX1_2V5: P2.98, R20.1
unnamed: C90.1, U8.E3
unnamed: C92.1, U8.A3
unnamed: C134.1, U4.5
unnamed: R2.1, U5.28
unnamed: R4.1, U6.28
unnamed: R6.1, U7.28
unnamed: R7.1, U1.3
unnamed: R8.1, U8.A4
unnamed: R9.1, U8.E4
unnamed: R10.1, U1.4
unnamed: R12.1, U1.5
unnamed: R13.1, U1.6
unnamed: R14.1, U1.7
unnamed: R15.1, U1.8
unnamed: R16.2, R17.1, U3.5
unnamed: R18.1, U1.9
unnamed: R19.2, U9.7
unnamed: R20.2, U9.6
Python1_1V8: C3.1, C6.1, C8.1, C15.1, C19.1, C21.1, C28.1, FB3.2, U5.6, U5.22, U5.26
Python1_CS#: P2.80, U1.16
Python1_CS#_3V3: R15.2, U5.47
Python1_DOUT0+: P2.44, U5.9
Python1_DOUT0-: P2.46, U5.10
Python1_DOUT1+: P2.50, U5.11
Python1_DOUT1-: P2.52, U5.12
Python1_DOUT2+: P2.56, U5.13
Python1_DOUT2-: P2.58, U5.14
Python1_DOUT3+: P2.62, U5.15
Python1_DOUT3-: P2.64, U5.16
Python1_Monitor0_3V3: P3.1, U5.44
Python1_Monitor1_3V3: P3.2, U5.45
Python1_SYNC+: P2.68, U5.17
Python1_SYNC-: P2.70, U5.18
Python1_VDD: C1.1, C4.1, C9.1, C13.1, C14.1, C18.1, C22.1, C25.1, C27.1, C30.1, FB1.2, P3.3, U5.1, U5.19, U5.29, U5.36
Python1_VDDPIX: C2.1, C5.1, C7.1, C10.1, C17.1, C20.1, C23.1, C26.1, C29.1, C31.1, FB2.2, U5.31, U5.33, U5.38, U5.40
Python1_clk_return+: P2.38, U5.7
Python1_clk_return-: P2.40, U5.8
Python1_lvds_clk+: R1.2, U2.14, U5.24
Python1_lvds_clk-: R1.1, U2.15, U5.23
Python2_1V8: C34.1, C37.1, C39.1, C45.1, C48.1, C53.1, C57.1, FB6.2, U6.6, U6.22, U6.26
Python2_CS#: P2.84, U1.18
Python2_CS#_3V3: R13.2, U6.47
Python2_DOUT0+: P2.9, U6.9
Python2_DOUT0-: P2.11, U6.10
Python2_DOUT1+: P2.15, U6.11
Python2_DOUT1-: P2.17, U6.12
Python2_DOUT2+: P2.21, U6.13
Python2_DOUT2-: P2.23, U6.14
Python2_DOUT3+: P2.33, U6.15
Python2_DOUT3-: P2.35, U6.16
Python2_Monitor0_3V3: P5.1, U6.44
Python2_Monitor1_3V3: P5.2, U6.45
Python2_SYNC+: P2.29, U6.17
Python2_SYNC-: P2.27, U6.18
Python2_VDD: C32.1, C35.1, C40.1, C43.1, C44.1, C47.1, C51.1, C54.1, C56.1, C59.1, FB4.2, P5.3, U6.1, U6.19, U6.29, U6.36
Python2_VDDPIX: C33.1, C36.1, C38.1, C41.1, C46.1, C49.1, C52.1, C55.1, C58.1, C60.1, FB5.2, U6.31, U6.33, U6.38, U6.40
Python2_clk_return+: P2.39, U6.7
Python2_clk_return-: P2.41, U6.8
Python2_lvds_clk+: R3.2, U2.7, U6.24
Python2_lvds_clk-: R3.1, U2.6, U6.23
Python3_1V8: C63.1, C66.1, C68.1, C74.1, C77.1, C79.1, C86.1, FB9.2, U7.6, U7.22, U7.26
Python3_CS#: P2.82, U1.17
Python3_CS#_3V3: R14.2, U7.47
Python3_DOUT0+: P2.34, U7.9
Python3_DOUT0-: P2.32, U7.10
Python3_DOUT1+: P2.28, U7.11
Python3_DOUT1-: P2.26, U7.12
Python3_DOUT2+: P2.22, U7.13
Python3_DOUT2-: P2.20, U7.14
Python3_DOUT3+: P2.16, U7.15
Python3_DOUT3-: P2.14, U7.16
Python3_Monitor0_3V3: P6.1, U7.44
Python3_Monitor1_3V3: P6.2, U7.45
Python3_SYNC+: P2.10, U7.17
Python3_SYNC-: P2.8, U7.18
Python3_VDD: C61.1, C64.1, C69.1, C72.1, C73.1, C76.1, C80.1, C83.1, C85.1, C88.1, FB7.2, P6.3, U7.1, U7.19, U7.29, U7.36
Python3_VDDPIX: C62.1, C65.1, C67.1, C70.1, C75.1, C78.1, C81.1, C84.1, C87.1, C89.1, FB8.2, U7.31, U7.33, U7.38, U7.40
Python3_clk_return+: P2.2, U7.7
Python3_clk_return-: P2.4, U7.8
Python3_lvds_clk+: R5.2, U2.11, U7.24
Python3_lvds_clk-: R5.1, U2.12, U7.23
Python_RST#: P2.74, U1.14
Python_RST#_3V3: U1.10, U5.46, U6.46, U7.46
Python_Trigger: P2.76, U1.15
Python_Trigger_3V3: R18.2, U5.41, U6.41, U7.41
Python_lvds_clk+: P2.45, R11.2, U2.3
Python_lvds_clk-: P2.47, R11.1, U2.2
SPI_MISO: P2.100, R19.1
SPI_MISO_3V3: U5.3, U6.3, U7.3, U9.2
SPI_MOSI: P2.92, U1.20
SPI_MOSI_3V3: R10.2, U5.2, U6.2, U7.2
SPI_SCK: P2.88, U1.19
SPI_SCK_3V3: R12.2, U5.4, U6.4, U7.4
